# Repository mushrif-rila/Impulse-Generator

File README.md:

# Impulse Generator
 During my 5th Semester Electronic circuit design module i have did this project

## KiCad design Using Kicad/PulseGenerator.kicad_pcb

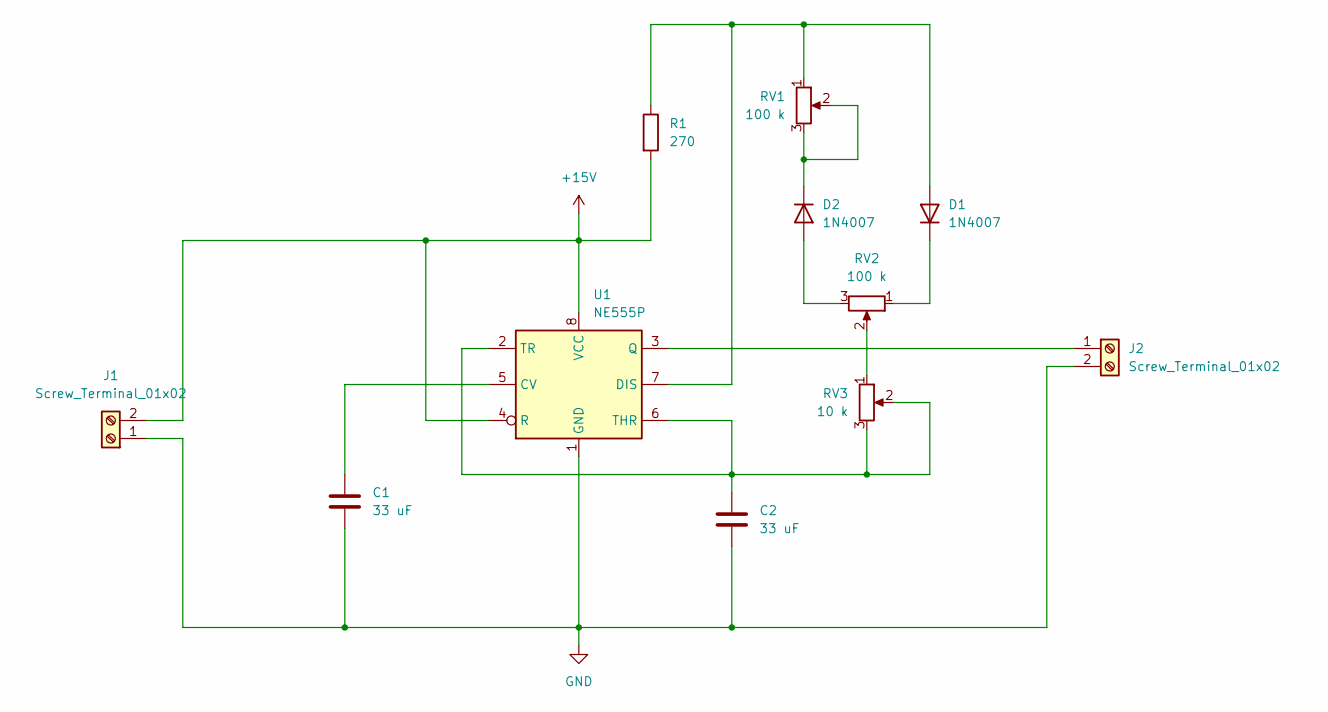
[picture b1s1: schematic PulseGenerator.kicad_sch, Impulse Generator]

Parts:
C1, C2: 33 uF; CP_Axial_L10.0mm_D4.5mm_P15.00mm_Horizontal
D1, D2: 1N4007; D_DO-41_SOD81_P10.16mm_Horizontal
J1, J2: Screw_Terminal_01x02; TerminalBlock_bornier-2_P5.08mm
R1: 270; R_Axial_DIN0204_L3.6mm_D1.6mm_P7.62mm_Horizontal
RV1, RV2: 100 k; Potentiometer_Alps_RK163_Single_Horizontal
RV3: 10 k; Potentiometer_Alps_RK163_Single_Horizontal
U1: NE555P; DIP-8_W7.62mm

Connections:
+15V: J1.2, R1.2, U1.4 (R), U1.8 (VCC)
GND: C1.2, C2.2, J1.1, J2.2, U1.1 (GND)
unnamed: D1.2 (A), R1.1, RV1.1, U1.7 (DIS)
unnamed: D1.1 (K), RV2.1
unnamed: D2.2 (A), RV2.3
unnamed: D2.1 (K), RV1.2, RV1.3
unnamed: J2.1, U1.3 (Q)
unnamed: RV2.2, RV3.1
unnamed: C1.1, U1.5 (CV)
unnamed: C2.1, RV3.2, RV3.3, U1.2 (TR), U1.6 (THR)

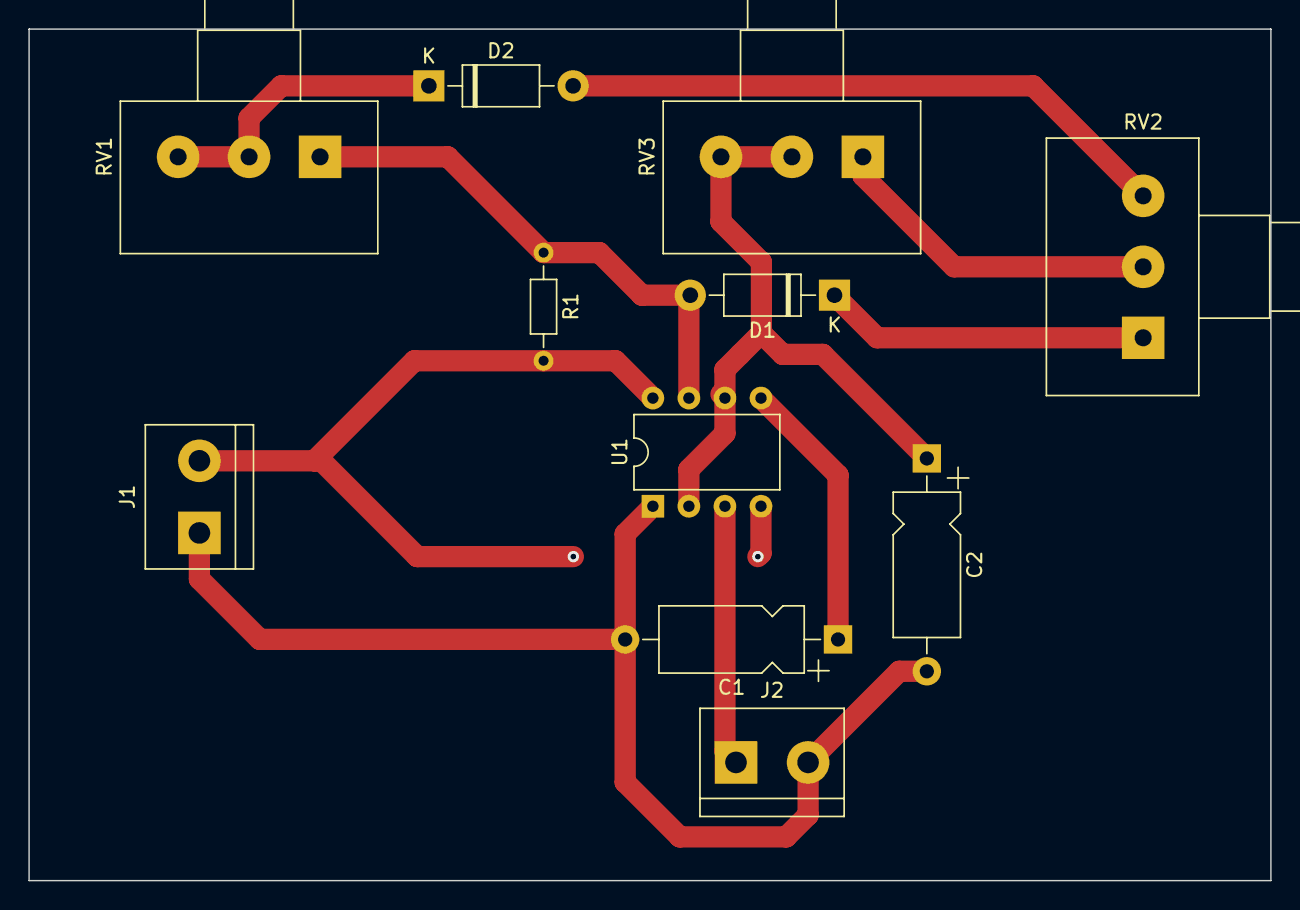
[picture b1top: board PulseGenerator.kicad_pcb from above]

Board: 2 copper layers, 87.5 x 60.0 mm, 11 parts (0 on the bottom side), 10 nets.

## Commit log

2025-01-04 Added Schematic file of Impulse Generator
2025-01-05 This is contain kicad schematic and pcb file
